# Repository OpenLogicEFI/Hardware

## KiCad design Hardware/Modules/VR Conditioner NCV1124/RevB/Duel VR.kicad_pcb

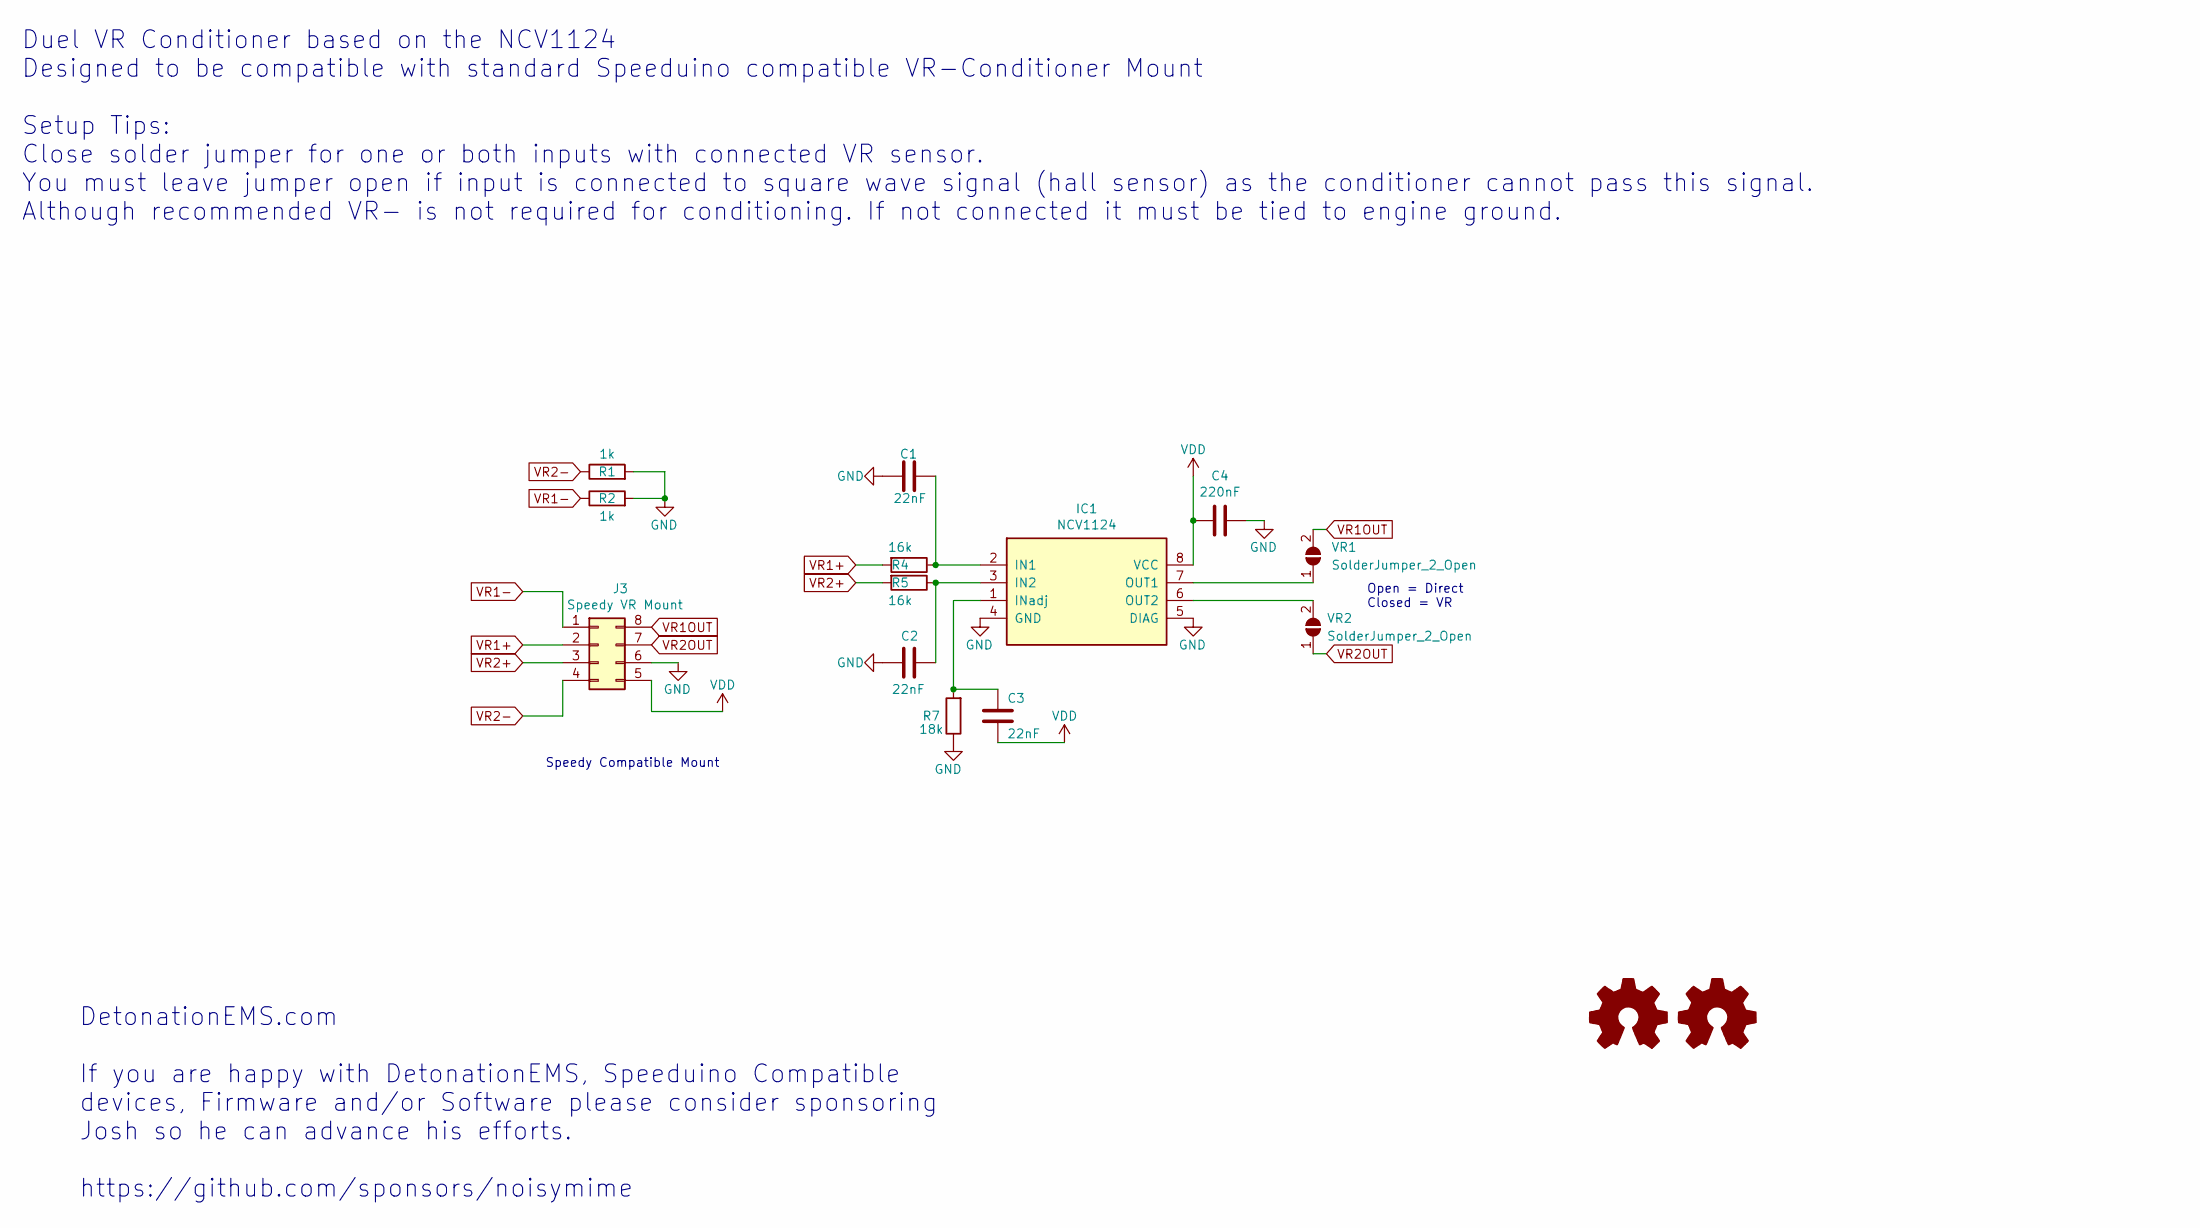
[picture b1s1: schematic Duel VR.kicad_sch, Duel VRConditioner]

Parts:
C1, C2, C3: 22nF; C_0603_1608Metric; LCSC C21122
C4: 220nF; C_0603_1608Metric; LCSC C21120
G1: Logo_Open_Hardware_Small; SpeeduinoCompatible-14mm
G2: Logo_Open_Hardware_Small; DetonationEMS-17mm
IC1: NCV1124; SO-8_3.9x4.9mm_P1.27mm
J3: Speedy VR Mount; DIP-8_W7.62mm_Socket_VRConditioner
R1, R2: 1k; R_1206_3216Metric; LCSC C4410
R4, R5: 16k; R_1210_3225Metric; LCSC C230406
R7: 18k; R_0603_1608Metric; LCSC C25810
VR1, VR2: SolderJumper_2_Open; SolderJumper-2_P1.3mm_Open_RoundedPad1.0x1.5mm

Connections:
GND: C1.1, C2.2, C4.2, IC1.4 (GND), IC1.5 (DIAG), J3.6, R1.2, R2.2, R7.1
unnamed: C1.2, IC1.2 (IN1), R4.1
unnamed: C2.1, IC1.3 (IN2), R5.1
unnamed: C3.1, IC1.1 (INadj), R7.2
unnamed: IC1.7 (OUT1), VR1.1 (A)
unnamed: IC1.6 (OUT2), VR2.2 (B)
VDD: C3.2, C4.1, IC1.8 (VCC), J3.5
VR1+: J3.2, R4.2
VR1-: J3.1, R2.1
VR1OUT: J3.8, VR1.2 (B)
VR2+: J3.3, R5.2
VR2-: J3.4, R1.1
VR2OUT: J3.7, VR2.1 (A)

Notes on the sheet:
Duel VR Conditioner based on the NCV1124 Designed to be compatible with standard Speeduino compatible VR-Conditioner Mount Setup Tips: Close solder jumper for one or both inputs with connected VR sensor. You must leave jumper open if input is connected to square wave signal (hall sensor) as the con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
Open = Direct Closed = VR
DetonationEMS.com If you are happy with DetonationEMS, Speeduino Compatible devices, Firmware and/or Software please consider sponsoring Josh so he can advance his efforts. https://github.com/sponsors/noisymime
Speedy Compatible Mount

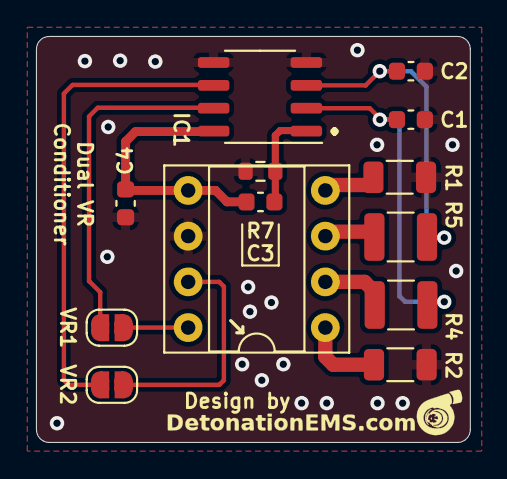
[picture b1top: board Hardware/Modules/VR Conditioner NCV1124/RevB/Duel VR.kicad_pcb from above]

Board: 2 copper layers, 24.1 x 22.6 mm, 15 parts (1 on the bottom side), 13 nets.

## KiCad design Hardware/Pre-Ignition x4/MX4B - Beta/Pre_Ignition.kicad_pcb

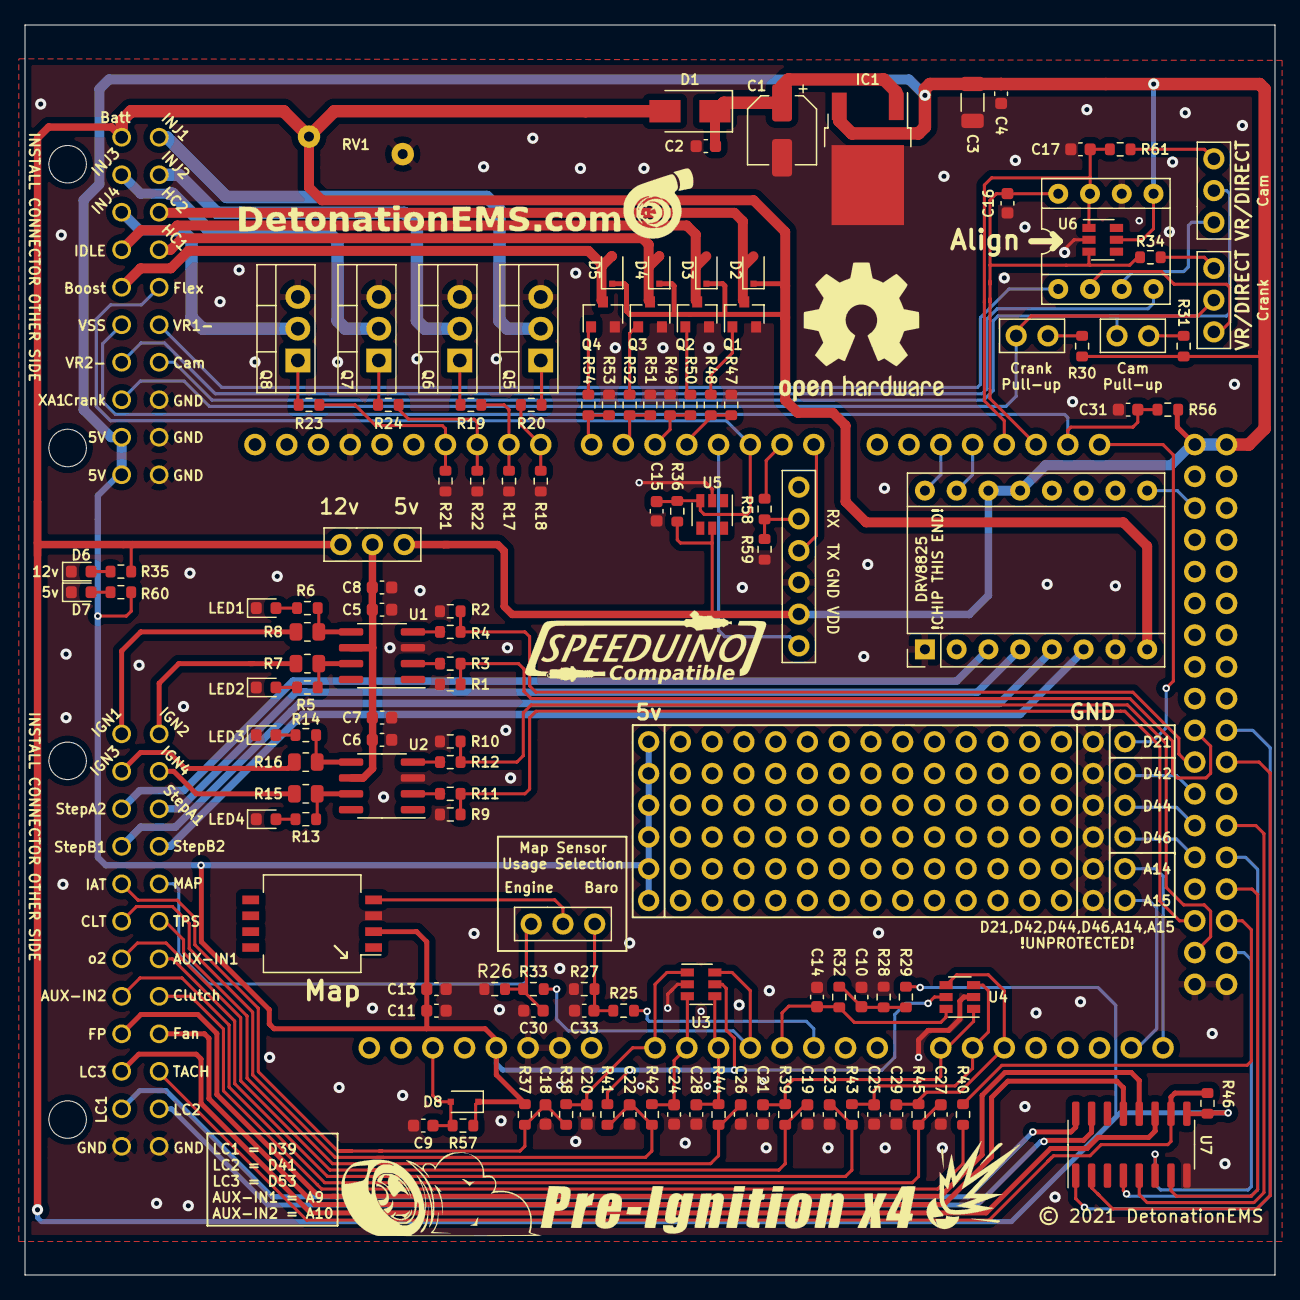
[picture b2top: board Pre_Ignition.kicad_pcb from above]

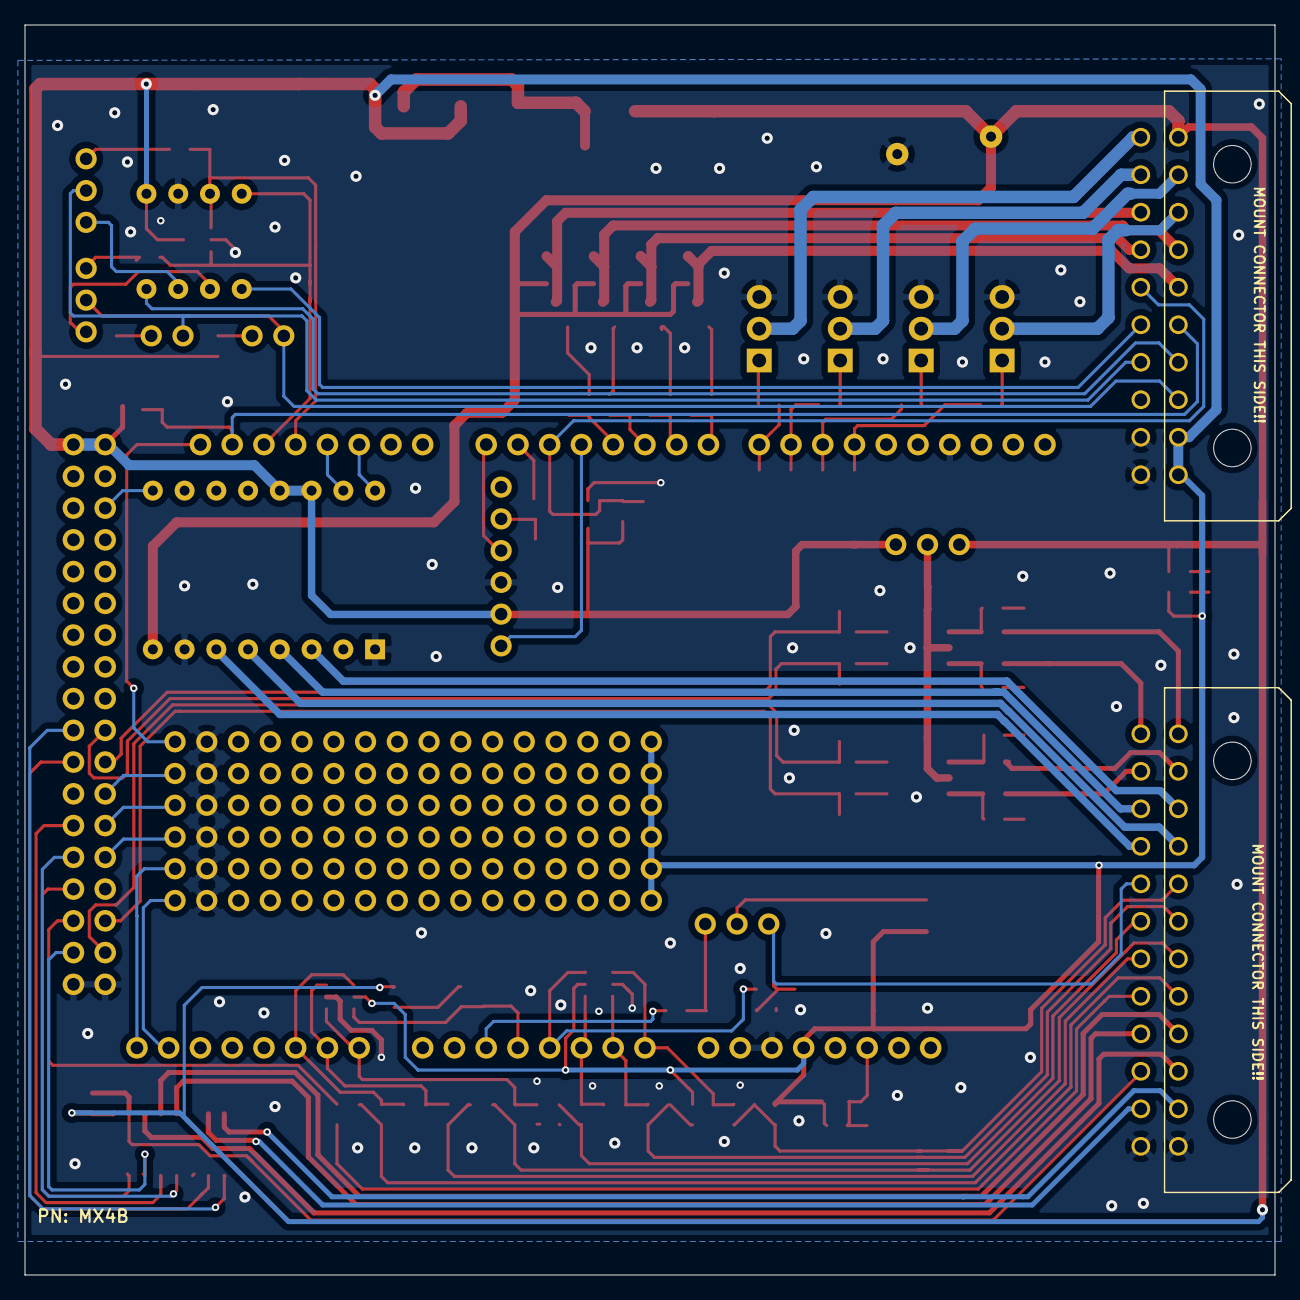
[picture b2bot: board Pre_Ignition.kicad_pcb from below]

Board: 2 copper layers, 100.0 x 100.0 mm, 141 parts (2 on the bottom side), 116 nets.

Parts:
A1: Pololu_Breakout_DRV8825; Pololu_Breakout-16_15.2x20.3mm
C1: 10uF; CP_Elec_5x5.3
C2: 330nF; C_0603_1608Metric
C3: 47uF; C_1206_3216Metric
C4, C5, C7, C10, C11, C17, C18, C19, C22, C23, C26, C27: 100nF; C_0603_1608Metric
C6, C8, C13: 1uF; C_0603_1608Metric
C9: 4.7nF; C_0603_1608Metric
C14, C15, C20, C21, C24, C25, C28, C29: 220nF; C_0603_1608Metric
C16, C31: 10nF; C_0603_1608Metric
C30, C33: 47pF; C_0603_1608Metric
D1: SS34; D_SMA
D2, D3, D4, D5, D8: 1N4148WS; D_SOD-323F
D6, D7: LED; LED_0603_1608Metric
G1: Logo_Open_Hardware_Small; DetonationEMS
G2: Logo_Open_Hardware_Small; TireSmoke-22mm
G3: Logo_Open_Hardware_Small; Boom8mm
G4: Logo_Open_Hardware_Small; SpeeduinoCompatible-21mm
G5: Logo_Open_Hardware_Small; Pre-IgnitionX4-30mm
G6: Logo_Open_Hardware_Small; OSHW-Logo2_14.6x12mm_SilkScreen
IC1: L7805CDT; TO-252-2
J2: Conn_01x04; Header-1x6-P2.54mm
J3, J6: Conn_02x16_Counter_Clockwise; PROTO-3X16
J4: VR_Header; Socket_VRConditioner
J5: Conn_02x12_Counter_Clockwise; Molex_Micro-Fit_3.0_43045-2400_2x12_P3.00mm_Horizontal
J7: Conn_02x10_Counter_Clockwise; Molex_Micro-Fit_3.0_43045-2000_2x10_P3.00mm_Horizontal
JP1: Ignition Voltage; 3-PinSwitch
JP2, JP3: VR/DIRECT; 3x1-GPIO
JP4, JP5: Pullup; 1x02-Proto
JP7: Jumper_3_Bridged12; 3-PinSwitch
LED1, LED2, LED3, LED4: LED; LED_0603_1608Metric
Map1: Map; Freescale_98ARH99066A
Q1, Q2, Q3, Q4: AO3400A; SOT-23
Q5, Q6, Q7, Q8: STP62NS04Z; TO-220-3_Vertical
R1, R2, R9, R10, R17, R18, R21, R22, R47, R49, R51, R53: 100K; R_0603_1608Metric
R3, R4, R11, R12, R19, R20, R23, R24, R28, R30, R31, R35, R40, R56, R58: 1k; R_0603_1608Metric
R5, R6, R13, R14, R36, R37, R41: 2.49k; R_0603_1608Metric
R7, R8, R15, R16: 22; R_0805_2012Metric
R25, R32, R33, R34, R38, R39, R42, R43, R44, R45, R60, R61: 470; R_0603_1608Metric
R26, R27: 51k; R_0603_1608Metric
R29: 3.9k; R_0603_1608Metric
R46: 10K; R_0603_1608Metric
R48, R50, R52, R54: 120; R_0603_1608Metric
R57: 10k; R_0603_1608Metric
R59: 2K; R_0603_1608Metric
RV1: MOV
U1, U2: TC4427; SOIC-8_3.9x4.9mm_P1.27mm
U3, U4, U5, U6: SRV05-4-P-T7; SOT-23-6
U7: ULN2003A; SOIC-16_3.9x9.9mm_P1.27mm
XA1: Arduino_Mega2560_Shield-Arduino; Arduino_Mega2560_Shield_IO_Only_No_Silk_Screen

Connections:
+BATT: A1.8, D1.2, D2.1, D3.1, D4.1, D5.1, J7.1, JP1.1, R29.2, R35.2, R46.2, RV1.1, U7.9
A9: C23.1, J5.19, R43.2
A10: C27.1, J5.8, R45.2
BOOST: D5.2, J7.5, Q4.3
CLT: C22.1, J5.6, R41.1, R42.2
Cam-In: J7.17, JP3.2, JP5.1
Clutch: J5.20, R40.2
Crank-In: J7.8, JP2.2, JP4.1
D39: J5.11, U7.16
D41: J5.23, U7.15
D53: J5.10, U7.11
Fan: J5.21, U7.13
Flex: C15.1, J7.15, R36.2, U5.3, XA1.D2
Fuel-Pump: J5.9, U7.12
GND: A1.1, A1.7, C1.2, C2.2, C3.2, C4.2, C5.2, C6.2, C7.2, C8.2, C9.1, C10.2, C11.1, C13.1, C14.2, C15.2, C16.1, C17.1, C18.2, C19.2, C20.2, C21.2, C22.2, C23.2, C24.2, C25.2, C26.2, C27.2, C28.2, C29.2, C30.2, C31.2, C33.2, D6.1, D7.1, IC1.2, J2.3, J3.15, J3.31, J3.47, J4.6, J5.12, J5.24, J6.15, J6.31, J6.47, J7.18, J7.19, J7.20, LED1.1, LED2.1, LED3.1, LED4.1, Map1.3, Q1.2, Q2.2, Q3.2, Q4.2, Q5.3, Q6.3, Q7.3, Q8.3, R1.2, R2.1, R9.2, R10.1, R17.2, R18.1, R21.2, R22.1, R26.1, R27.2, R28.1, R47.1, R49.1, R51.1, R53.1, R59.1, RV1.2, U1.3, U2.3, U3.2, U4.2, U5.2, U6.2, U7.8, XA1.GND1, XA1.GND2, XA1.GND3, XA1.GND5, XA1.GND6
HC1: D4.2, J7.14, Q3.3
HC2: D2.2, J7.13, Q1.3
IAT: C18.1, J5.5, R37.1, R38.2
IDLE: D3.2, J7.4, Q2.3
IGN1: J5.1, R8.1
IGN2: J5.13, R7.1
IGN3: J5.2, R16.1
IGN4: J5.14, R15.1
IGN-V-Select: C5.1, C6.1, C7.1, C8.1, JP1.2, U1.6, U2.6
INJ1: J7.11, Q5.2
INJ2: J7.12, Q6.2
INJ3: J7.2, Q7.2
INJ4: J7.3, Q8.2
MC-A0: C20.1, R38.1, U3.1, XA1.A0
MC-A1: C24.1, R42.1, U3.3, XA1.A1
MC-A2: C28.1, R44.1, U3.4, XA1.A2
MC-A3: R33.2, U3.6, XA1.A3
MC-A4: C14.1, R32.1, U4.6, XA1.A4
MC-A5: R25.2, XA1.A5
MC-A8: C21.1, R39.1, U4.1, XA1.A8
MC-A9: C25.1, R43.1, U4.3, XA1.A9
MC-A10: C29.1, R45.1, U4.4, XA1.A10
MC-A14: J3.48, XA1.A14
MC-A15: J3.32, XA1.A15
MC-D0: J2.4, XA1.D0
MC-D1: R58.2, XA1.D1
MC-D3: J2.1, XA1.D3
MC-D4: R47.2, R48.2, XA1.D4
MC-D5: R49.2, R50.2, XA1.D5
MC-D6: R51.2, R52.2, XA1.D6
MC-D7: R53.2, R54.2, XA1.D7
MC-D8: R18.2, R20.2, XA1.D8
MC-D9: R17.1, R19.2, XA1.D9
MC-D10: R22.2, R24.2, XA1.D10
MC-D11: R21.1, R23.2, XA1.D11
MC-D16: A1.16, XA1.D16
MC-D17: A1.15, XA1.D17
MC-D18: C17.2, J4.7, R61.1, U6.1, XA1.D18
MC-D19: C16.2, J4.8, R34.1, U6.3, XA1.D19
MC-D20: C31.1, J7.6, R56.1, XA1.D20
MC-D21: J6.16, XA1.D21
MC-D24: A1.9, XA1.D24
MC-D38: R1.1, R3.2, XA1.D38
MC-D39: U7.1, XA1.D39
MC-D40: R2.2, R4.2, XA1.D40
MC-D41: U7.2, XA1.D41
MC-D42: J6.32, XA1.D42
MC-D44: J6.48, XA1.D44
MC-D45: U7.5, XA1.D45
MC-D46: J3.16, XA1.D46
MC-D47: U7.4, XA1.D47
MC-D49: U7.7, XA1.D49
MC-D50: R9.1, R11.2, XA1.D50
MC-D51: R40.1, XA1.D51
MC-D52: R10.2, R12.2, XA1.D52
MC-D53: U7.6, XA1.D53
MC-RESET: C9.2, D8.2, R57.2, XA1.RST1
Map-External: C30.1, J5.17, JP7.1, R26.2, R33.1
unnamed: C1.1, C2.1, D1.1, IC1.1
unnamed: C10.1, R28.2, R29.1, R32.2
unnamed: C33.1, JP7.3, R25.1, R27.1
unnamed: D6.2, R35.1
unnamed: D7.2, R60.1
unnamed: J2.5, R58.1, R59.2
unnamed: J4.2, JP2.3
unnamed: J4.3, JP3.1
unnamed: JP2.1, R34.2
unnamed: JP3.3, R61.2
unnamed: JP4.2, R30.1
unnamed: JP5.2, R31.1
unnamed: JP7.2, Map1.4
unnamed: LED1.2, R6.1
unnamed: LED2.2, R5.2
unnamed: LED3.2, R14.1
unnamed: LED4.2, R13.2
unnamed: Q1.1, R48.1
unnamed: Q2.1, R50.1
unnamed: Q3.1, R52.1
unnamed: Q4.1, R54.1
unnamed: Q5.1, R20.1
unnamed: Q6.1, R19.1
unnamed: Q7.1, R24.1
unnamed: Q8.1, R23.1
unnamed: R3.1, U1.2
unnamed: R4.1, U1.4
unnamed: R5.1, R7.2, U1.7
unnamed: R6.2, R8.2, U1.5
unnamed: R11.1, U2.2
unnamed: R12.1, U2.4
unnamed: R13.1, R15.2, U2.7
unnamed: R14.2, R16.2, U2.5
O2: C19.1, J5.7, R39.2
Step-A1: A1.4, J5.15
Step-A2: A1.3, J5.3
Step-B1: A1.5, J5.4
Step-B2: A1.6, J5.16
TPS: C26.1, J5.18, R44.2
Tach: J5.22, R46.1, U7.10
VDD: A1.13, A1.14, C3.1, C4.1, C11.2, C13.2, D8.1, IC1.3, J2.2, J3.1, J3.17, J3.33, J4.5, J6.1, J6.17, J6.33, J7.9, J7.10, JP1.3, Map1.2, R30.2, R31.2, R36.1, R37.2, R41.2, R56.2, R57.1, R60.2, U3.5, U4.5, U5.5, U6.5, XA1.5V1, XA1.5V3, XA1.5V4
VR1-: J4.1, J7.16
VR2-: J4.4, J7.7

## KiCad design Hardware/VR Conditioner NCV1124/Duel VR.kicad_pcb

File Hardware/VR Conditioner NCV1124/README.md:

# VR Conditioner
Based on the NCV1124 Chip

Pin Setup:
     This Conditioner is capable of conditioning two variable reluctance inputs but cannot pass through other signal types such as hall (square) signals. If one of your inputs is NOT a VR signal do NOT populate both input and output pins for that signal.

Crankshaft Position Sensor  - VR1+ / 1 OUT

Camshaft Position Sensor  - VR2+ / 2 OUT

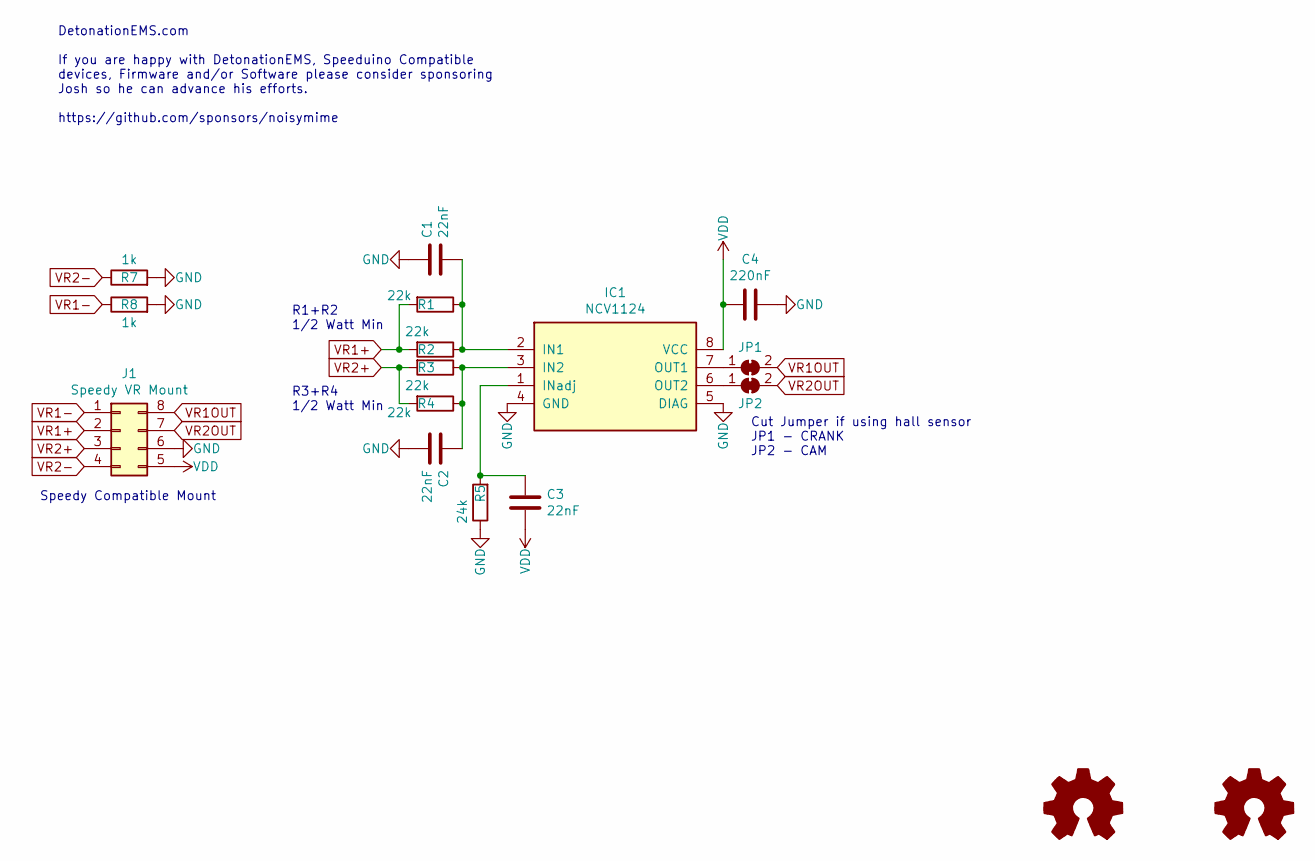
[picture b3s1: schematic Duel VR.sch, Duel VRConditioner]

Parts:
C1, C2, C3: 22nF; C_0603_1608Metric; LCSC C21122
C4: 220nF; C_0603_1608Metric; LCSC C21120
G1: Logo_Open_Hardware_Small; SpeeduinoCompatible-14mm
G2: Logo_Open_Hardware_Small; DetonationEMS-17mm
IC1: NCV1124; SO-8_3.9x4.9mm_P1.27mm; LCSC C152274
J1: Speedy VR Mount; DIP-8_W7.62mm_Socket_VRConditioner
JP1, JP2: SolderJumper_2_Bridged; SolderJumper-2_P1.3mm_Bridged_RoundedPad1.0x1.5mm
R1, R2, R3, R4: 22k; R_0805_2012Metric; LCSC C17560
R5: 24k; R_0603_1608Metric; LCSC C23352
R7, R8: 1k; R_0805_2012Metric; LCSC C17513

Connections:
GND: C1.1, C2.2, C4.2, IC1.4 (GND), IC1.5 (DIAG), J1.6, R5.1, R7.2, R8.2
unnamed: C1.2, IC1.2 (IN1), R1.1, R2.1
unnamed: C2.1, IC1.3 (IN2), R3.1, R4.1
unnamed: C3.1, IC1.1 (INadj), R5.2
unnamed: IC1.6 (OUT2), JP2.1 (A)
unnamed: IC1.7 (OUT1), JP1.1 (A)
VDD: C3.2, C4.1, IC1.8 (VCC), J1.5
VR1+: J1.2, R1.2, R2.2
VR1-: J1.1, R8.1
VR1OUT: J1.8, JP1.2 (B)
VR2+: J1.3, R3.2, R4.2
VR2-: J1.4, R7.1
VR2OUT: J1.7, JP2.2 (B)

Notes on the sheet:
Speedy Compatible Mount
R1+R2 1/2 Watt Min
R3+R4 1/2 Watt Min
Cut Jumper if using hall sensor JP1 - CRANK JP2 - CAM
DetonationEMS.com If you are happy with DetonationEMS, Speeduino Compatible devices, Firmware and/or Software please consider sponsoring Josh so he can advance his efforts. https://github.com/sponsors/noisymime

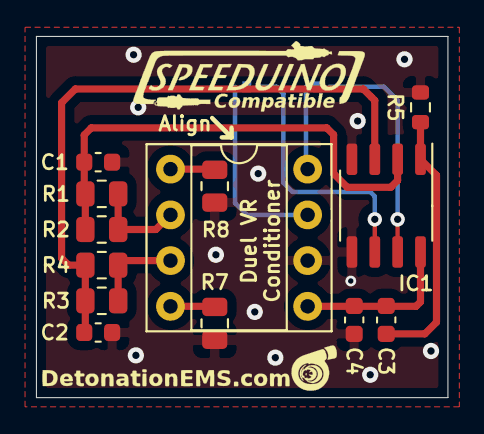
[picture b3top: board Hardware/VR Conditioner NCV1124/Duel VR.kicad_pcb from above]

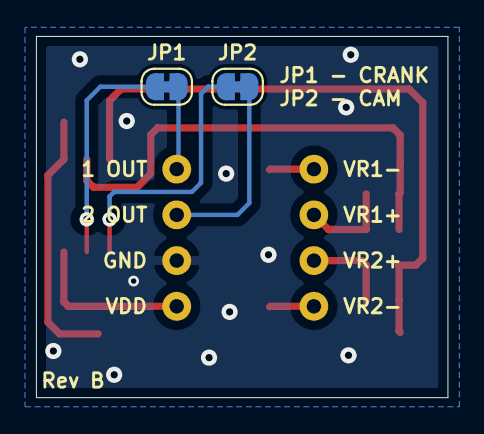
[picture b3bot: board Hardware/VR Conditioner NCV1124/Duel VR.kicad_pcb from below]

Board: 2 copper layers, 22.9 x 20.1 mm, 17 parts (2 on the bottom side), 13 nets.

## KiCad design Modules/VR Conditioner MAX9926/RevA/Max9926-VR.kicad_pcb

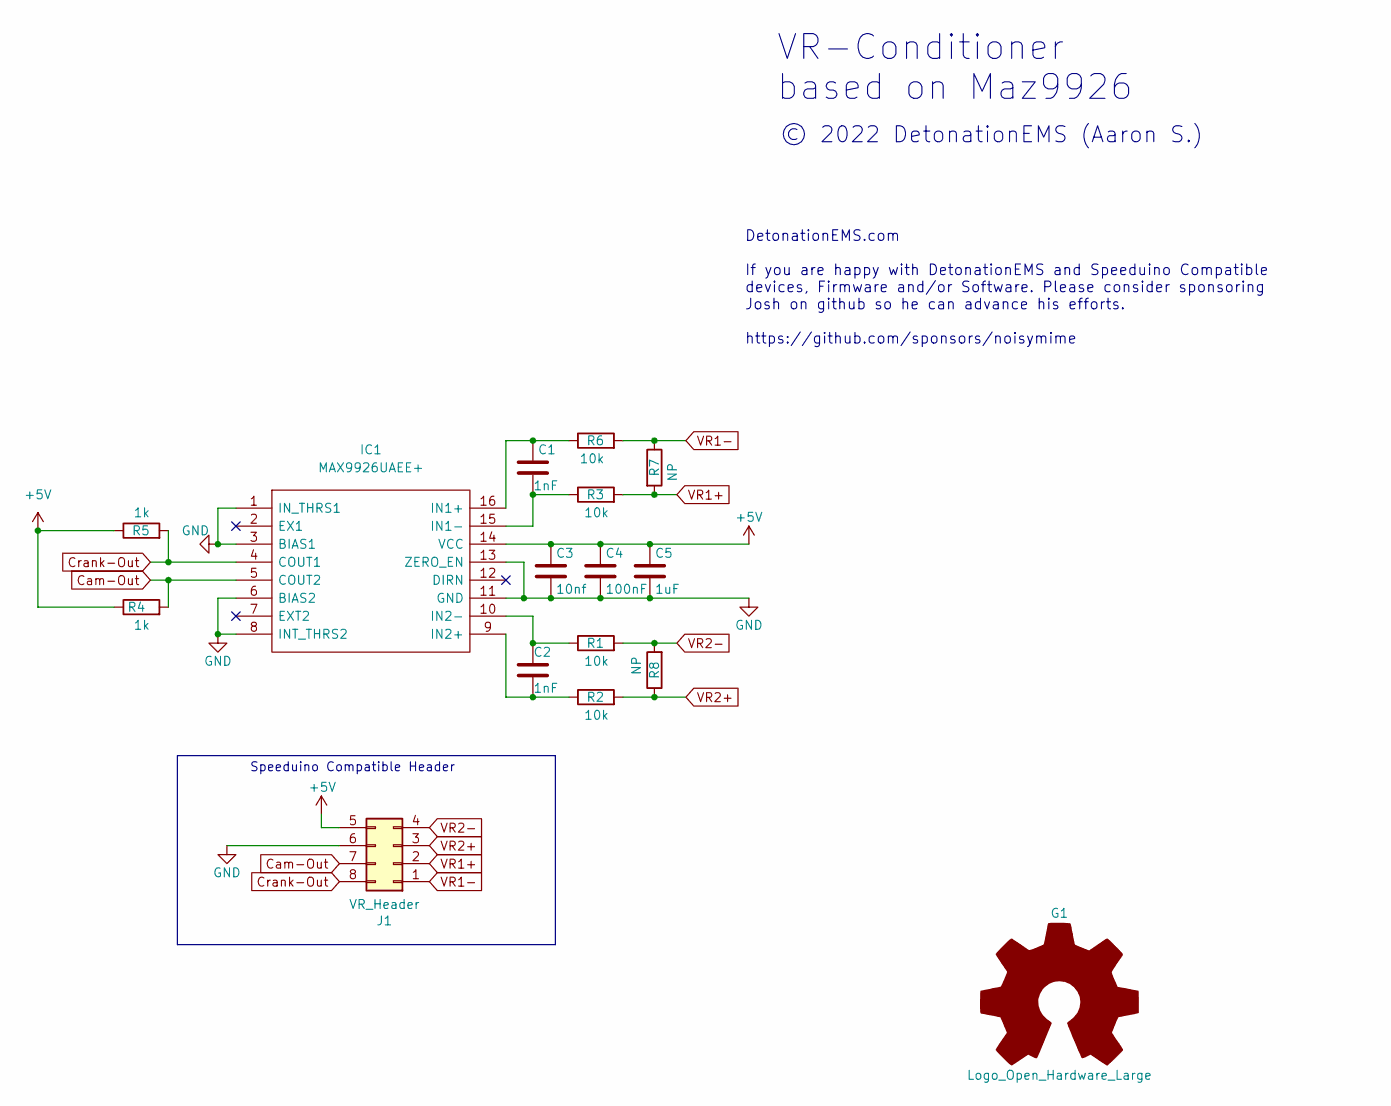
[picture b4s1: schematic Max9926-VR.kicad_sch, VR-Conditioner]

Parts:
C1, C2: 1nF; C_0603_1608Metric; LCSC C1588
C3: 10nf; C_0603_1608Metric; LCSC C57112
C4: 100nF; C_0603_1608Metric; LCSC C14663
C5: 1uF; C_0603_1608Metric; LCSC C15849
G1: Logo_Open_Hardware_Large; SpeeduinoCompatible-17mm
IC1: MAX9926UAEE+; SOP64P602X175-16N; MFG Part Num MAX9926UAEE+
J1: VR_Header; Socket_VRConditioner
R1, R2, R3, R6: 10k; R_1206_3216Metric; LCSC C17902
R4, R5: 1k; R_0402_1005Metric; LCSC C11702
R7, R8: NP; R_Axial_DIN0207_L6.3mm_D2.5mm_P7.62mm_Horizontal

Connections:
+5V: C3.1, C4.1, C5.1, IC1.14 (VCC), J1.5, R4.1, R5.1
Cam-Out: IC1.5 (COUT2), J1.7, R4.2
Crank-Out: IC1.4 (COUT1), J1.8, R5.2
GND: C3.2, C4.2, C5.2, IC1.1 (IN_THRS1), IC1.3 (BIAS1), IC1.6 (BIAS2), IC1.8 (INT_THRS2), IC1.11 (GND), IC1.13 (ZERO_EN), J1.6
unnamed: C1.1, IC1.16 (IN1+), R6.1
unnamed: C1.2, IC1.15 (IN1-), R3.1
unnamed: C2.1, IC1.10 (IN2-), R1.1
unnamed: C2.2, IC1.9 (IN2+), R2.1
VR1+: J1.2, R3.2, R7.2
VR1-: J1.1, R6.2, R7.1
VR2+: J1.3, R2.2, R8.1
VR2-: J1.4, R1.2, R8.2

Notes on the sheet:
© 2022 DetonationEMS (Aaron S.)
DetonationEMS.com If you are happy with DetonationEMS and Speeduino Compatible devices, Firmware and/or Software. Please consider sponsoring Josh on github so he can advance his efforts. https://github.com/sponsors/noisymime
Speeduino Compatible Header
VR-Conditioner based on Maz9926

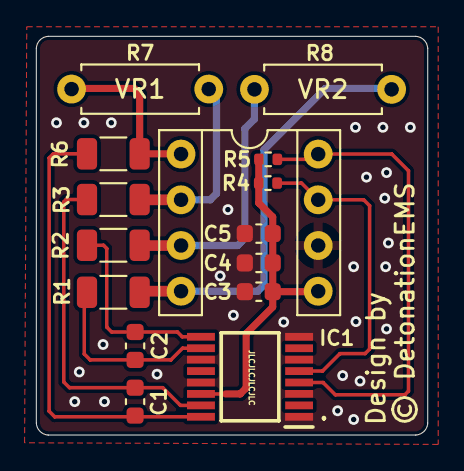
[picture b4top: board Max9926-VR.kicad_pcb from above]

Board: 2 copper layers, 21.7 x 22.1 mm, 16 parts (1 on the bottom side), 12 nets.

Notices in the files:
Hardware/Modules/VR Conditioner NCV1124/RevB/Duel VR.kicad_pcb:
©Aaron S. 2023
Hardware/Pre-Ignition x4/MX4B - Beta/Pre_Ignition.kicad_pcb:
© 2021 DetonationEMS
Modules/VR Conditioner MAX9926/RevA/Max9926-VR.kicad_pcb:
Design by
© DetonationEMS
